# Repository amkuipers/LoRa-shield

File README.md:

# LoRa shield for the WeMos D1 mini with a RFM95 module

DRAFT - WORK IN PROGRESS

 * Files here are older version, please use the order link for newer pcb version.
 * Order board v6.1

 <a href="https://oshpark.com/shared_projects/X4cLxyim"></img></a>

## Eagle 

Version 8.2.1

## Solder tips

 * RFM95 module
 * Capacitor for 3V3-GND optional
 * D3 jumper, leave open while programming ESP8266
 * SMA edge connector for antenna, or use a wire
 * Dual base shield optional
 
## Unused D1 mini pinouts

 * A0
 * D4
 * TX, RX
 * RST
 * 5V
 
 ## Credits are pending

 * Maarten things4u
 * D1 mini shield template

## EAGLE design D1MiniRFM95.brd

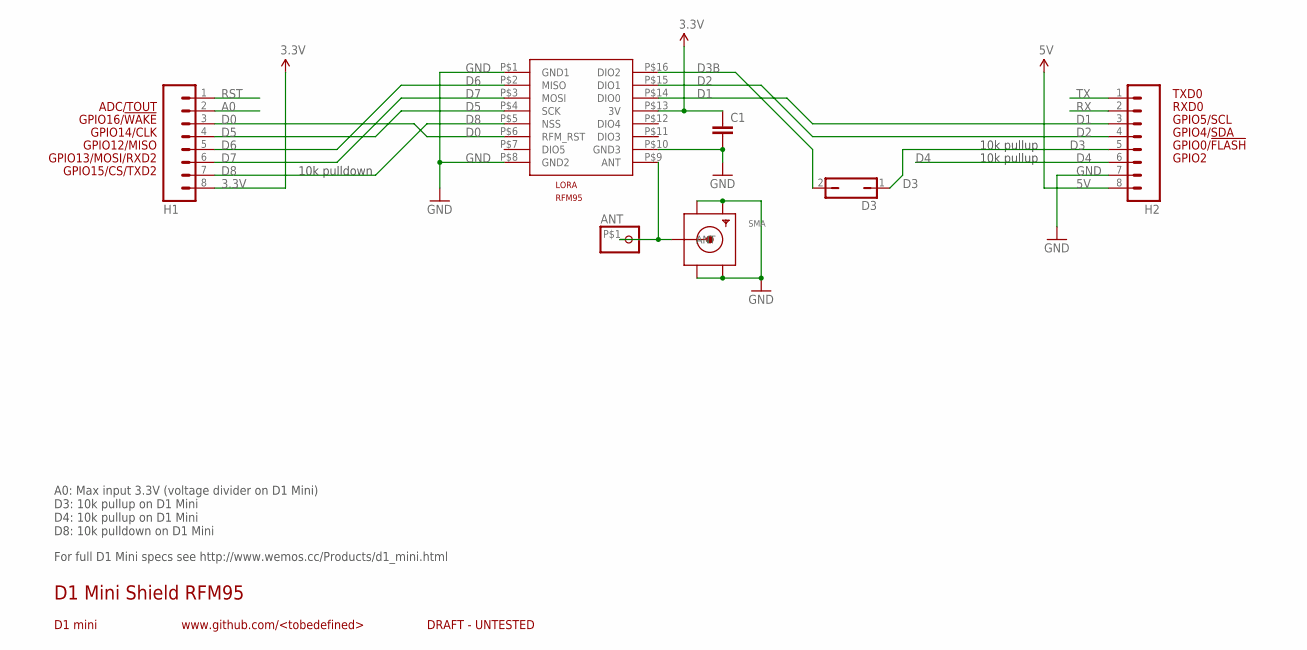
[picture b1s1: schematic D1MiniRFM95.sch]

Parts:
ANT: PINHD-1X1-BIGPOGO; 1X1-BIGPOGO
C1: C-EU025-024X044; C025-024X044
D3: JP1Q; JP1
H1, H2: M08; 1X08
LORA: RFM95
SMA: SMACONNECTOR_EDGE; SMA_EDGELAUNCH

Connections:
3.3V: C1.1, H1.8, LORA.P$13 (3V)
5V: H2.8
A0: H1.2
ANT: ANT.P$1, LORA.P$9 (ANT), SMA.P (ANT)
D0: H1.3, LORA.P$6 (RFM_RST)
D1: H2.3, LORA.P$14 (DIO0)
D2: H2.4, LORA.P$15 (DIO1)
D3: D3.1, H2.5
D3B: D3.2, LORA.P$16 (DIO2)
D4: H2.6
D5: H1.4, LORA.P$4 (SCK)
D6: H1.5, LORA.P$2 (MISO)
D7: H1.6, LORA.P$3 (MOSI)
D8: H1.7, LORA.P$5 (NSS)
GND: C1.2, H2.7, LORA.P$1 (GND1), LORA.P$8 (GND2), LORA.P$10 (GND3), SMA.GND@1 (GND4), SMA.GND@2 (GND3), SMA.GND@3 (GND2), SMA.GND@4 (GND1)
RST: H1.1
RX: H2.2
TX: H2.1

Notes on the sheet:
GPIO2
GPIO0/!FLASH
GPIO12/MISO
GPIO4/SDA
GPIO5/SCL
RXD0
TXD0
GPIO13/MOSI/RXD2
GPIO14/CLK
GPIO15/CS/TXD2
GPIO16/!WAKE
D1 mini
D1 Mini Shield RFM95
DRAFT - UNTESTED
www.github.com/<tobedefined>
ADC/TOUT
A0: Max input 3.3V (voltage divider on D1 Mini) D3: 10k pullup on D1 Mini D4: 10k pullup on D1 Mini D8: 10k pulldown on D1 Mini
10k pulldown
10k pullup
For full D1 Mini specs see http://www.wemos.cc/Products/d1_mini.html

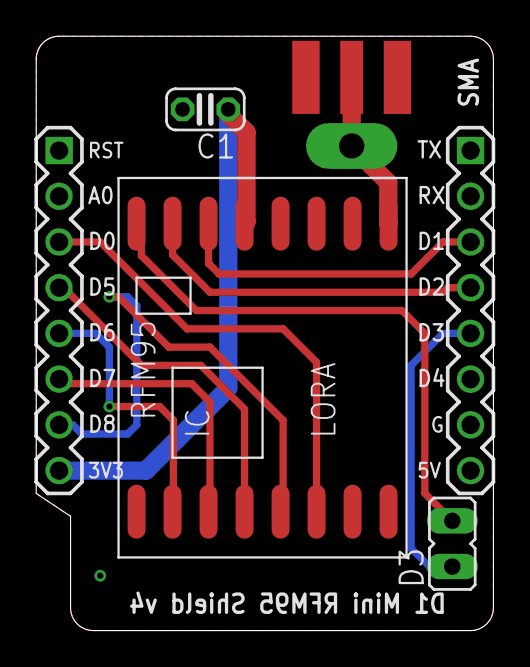
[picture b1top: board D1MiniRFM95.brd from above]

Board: 2 copper layers, 25.4 x 33.0 mm, 7 parts (0 on the bottom side), 12 nets.

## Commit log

2017-06-06 IoT-library
    Custom components
2017-06-06 D1Mini RFM95 v3
    This version is DRAFT only
2017-06-06 draft
2017-06-06 v4.01
2017-08-05 added link to order the latest board
2021-04-02 Add .whitesource configuration file
2021-06-06 add images of pcb

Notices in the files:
parts and their libraries:
freetronics-original: Licensing: CC v3.0 Share-Alike You are welcome to use this library for commercial purposes.
